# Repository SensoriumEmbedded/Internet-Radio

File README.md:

# Internet-Radio
ESP32 based WiFi Internet Radio with display, rotary encoder controls, and SD storage

## Stand-alone version:
|||
|--|--|
|||

## Full version incorporated in a 1941 Philco Radio case:
|||
|--|--|
|<video src="Pictures/1941 Philco/Internet Radio_01.mp4" title="1941 Philco project"></video>||

<video controls src="Pictures/1941 Philco/Internet Radio_01.mp4" title="Title"></video>

## Features
* Plays streaming MP3 stations
  * Large buffer for smooth playback
* Parses/displays displays meta data information
* Stores settings and favorite stations on SD card
* Can display pictures (jpg) and play MP3 files
* Displays time, synched from internet connection
* Remote control interface via TTL serial

## Operation
* "S" Rotary Encoder: Push to enter menu system/select.  Rotate to move "cursor"
* "C" Rotary Encoder: Turn (slowly) to select channels, like a dial.  push to stop streaming.
* Scan for wifi and enter a PW in the menu (among other things, explore away).
  * All the settings are saved to "NetRadio.txt" on the SD card. 

## Inspiration
* https://github.com/Edzelf/Esp-radio
* https://github.com/RalphBacon/205-Internet-Radio

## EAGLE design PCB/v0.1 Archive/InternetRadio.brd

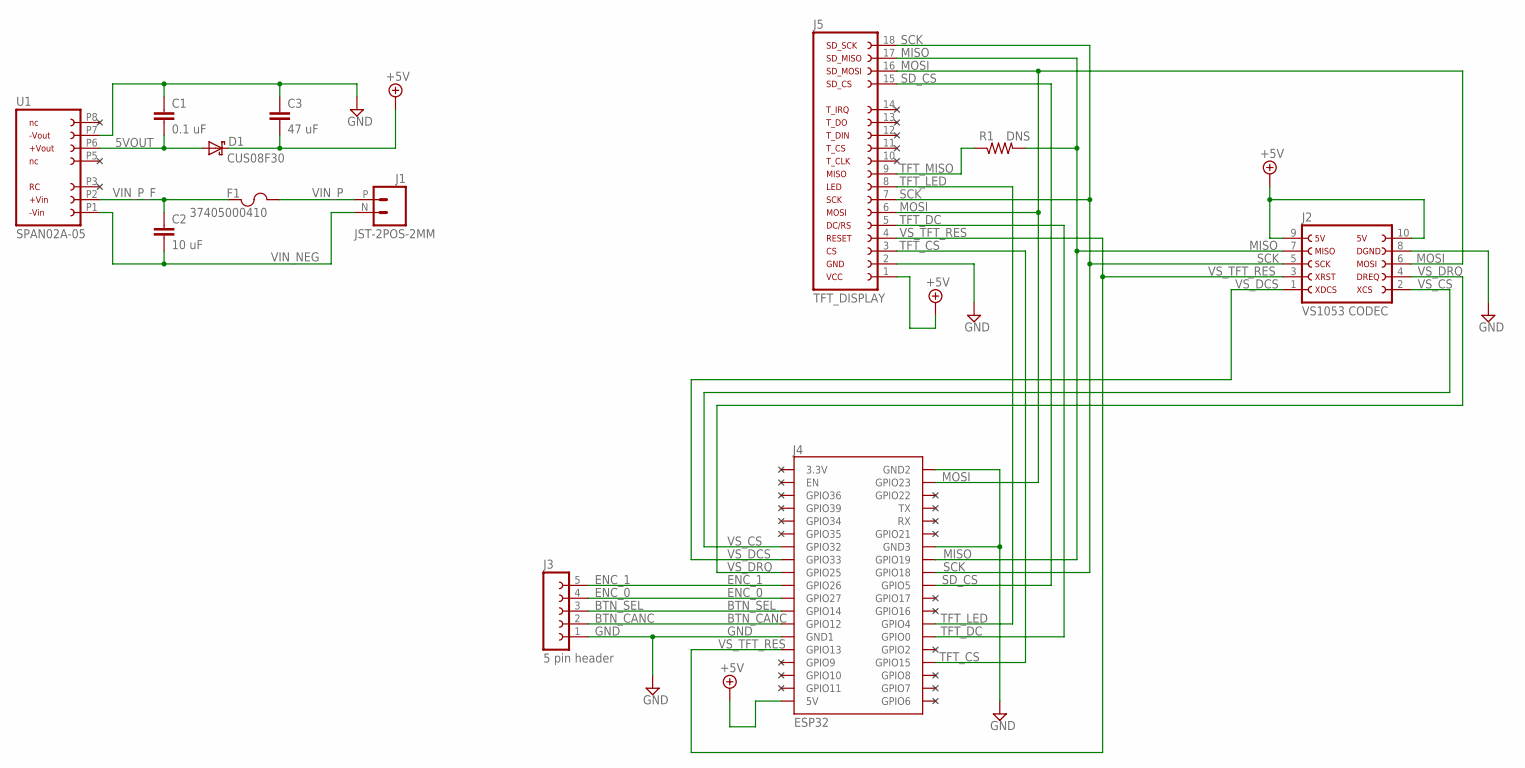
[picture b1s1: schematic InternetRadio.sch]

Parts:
C1: 0.1 uF; 0805
C2: 10 uF; 0805
C3: 47 uF; 0805
D1: CUS08F30; SOD-323
F1: 37405000410; FUS_LITTELFUSE_374_LTF
J1: JST-2POS-2MM; 89400-0220
J2: VS1053 CODEC; VS1053_MODULE
J3: 5 pin header; FE05-1
J4: ESP32
J5: TFT_DISPLAY; 3.5"_TFT_DISPLAY-NO_HOLES
R1: DNS; 0805
U1: SPAN02A-05

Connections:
5VOUT: C1.2, D1.A, U1.P6 (6)
+5V: C3.2, D1.C, J2.9, J2.10, J4.5V, J5.1
BTN_CANC: J3.2, J4.GPIO12
BTN_SEL: J3.3, J4.GPIO14
ENC_0: J3.4, J4.GPIO27
ENC_1: J3.5, J4.GPIO26
GND: C1.1, C3.1, J2.8, J3.1, J4.GND1, J4.GND2, J4.GND3, J5.2, U1.P7 (7)
MISO: J2.7, J4.GPIO19, J5.17, R1.2
MOSI: J2.6, J4.GPIO23, J5.6, J5.16
SCK: J2.5, J4.GPIO18, J5.7, J5.18
SD_CS: J4.GPIO5, J5.15
TFT_CS: J4.GPIO15, J5.3
TFT_DC: J4.GPIO0, J5.5
TFT_LED: J4.GPIO4, J5.8
TFT_MISO: J5.9, R1.1
VIN_NEG: C2.2, J1.N (1), U1.P1 (1)
VIN_P: F1.1, J1.P (2)
VIN_P_F: C2.1, F1.2, U1.P2 (2)
VS_CS: J2.2, J4.GPIO32
VS_DCS: J2.1, J4.GPIO33
VS_DRQ: J2.4, J4.GPIO25
VS_TFT_RES: J2.3, J4.GPIO13, J5.4

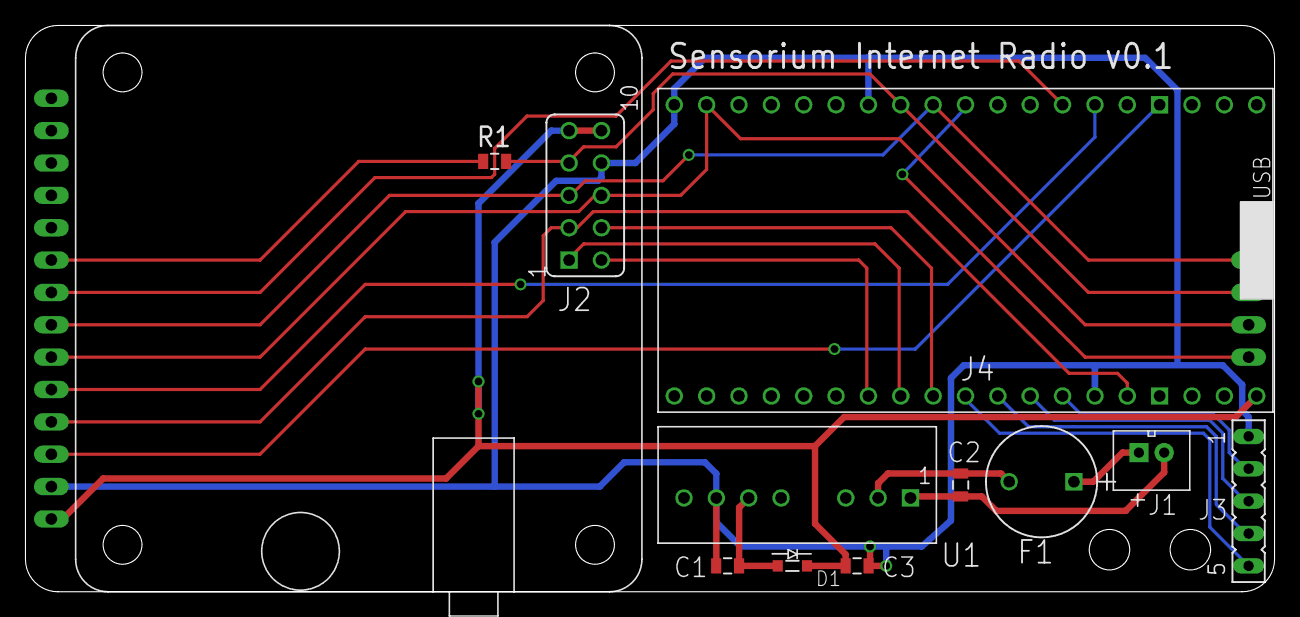
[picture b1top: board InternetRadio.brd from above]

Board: 2 copper layers, 98.0 x 44.5 mm, 12 parts (1 on the bottom side), 22 nets.

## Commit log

2025-07-27 Main Source, How to build
2025-07-27 Library additions
2025-07-27 PCB files
2025-07-27 SD card files
2025-07-27 Pictures
2025-07-27 readme updates
2025-07-28 readmetweak

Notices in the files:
parts and their libraries:
COPYRIGHT: Copyright (C) 2022 Ultra Librarian. All rights reserved.
